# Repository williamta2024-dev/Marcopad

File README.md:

# RP2040 ZERO 4x4 Mechanical Macropad

A custom-built, programmable 16-key mechanical macropad powered by the RP2040 ZERO. This project combines custom PCB design, 3D mechanical modeling, and embedded programming to create a versatile productivity tool.

## Features

* **4x4 Matrix Layout:** 16 fully programmable mechanical switches for shortcuts, macros, or media controls.
* **RP2040 ZERO:** High-performance microcontroller with native USB support.
* **Custom PCB:** Optimized layout for a compact footprint and reliable signal integrity.
* **3D Printed Enclosure:** A custom-designed case tailored specifically for the hardware assembly.
* **Customizable Firmware:** Easily adaptable for various workflows (streaming, coding, gaming).

## Hardware Specifications

| Component | Description |
| :--- | :--- |
| **Microcontroller** | RP2040 ZERO |
| **Switches** | 16x Mechanical Switches (MX-compatible) |
| **PCB** | Custom designed in KiCad |
| **Case** | 3D Printed (ONSHAPE) |
| **Connection** | USB-C |

## Getting Started

### Hardware Assembly
1.  **PCB Fabrication:** Order the PCB using the provided Gerber files in `/hardware/pcb`.
2.  **Soldering:** Solder the RP2040 ZERO and mechanical switches to the PCB.
3.  **Enclosure:** 3D print the top and bottom halves of the enclosure found in `/hardware/enclosure`.
4.  **Final Assembly:** Secure the PCB into the enclosure using M3 screws.

### Firmware Setup
1.  Connect the macropad to your computer via USB-C.
2.  Flash the firmware located in the `/firmware` directory using the Arduino IDE or by copying files if using C++.
3.  Configure your keymaps in the configuration file to match your desired shortcuts. S

### Schematic

### PCB  

### 3D Design

## Bill of Materials (BOM)

Here is the list of components, hardware, and materials required to build this project:

| Item | Component / Part | Description | Qty | Est. Cost | Source / Link |
| :--- | :--- | :--- | :--- | :--- | :--- |
| **1** | MACROPAD PCB-PTH_Y3 | The PCB | 3 | \$7.80 | [Link](https://cart.jlcpcb.com/shopcart/cartEdit/?id=4c4162048d664ba7a7ae664a28d13e49&type=1&changeType=1&achieveDate=48) |
| **2** | Estardyn RP2040-Zero RP2040 for Raspberry Pi Microcontroller PICO Development Board Module Dual-Core 2MB Flash |A raspberry pi for my macropad. | 1 | \$6.71 | [Link](https://www.aliexpress.us/item/3256811972442631.html) |
| **3** |20-100pc Mechanical Keyboard Switches Blue Red Brown Switch Customizable Hot-Swappable 3 Pins Cross Stem for Mechanical Keyboard |Keyswitches for the Macropad | 1 | \$0.99| [Link](https://www.aliexpress.us/item/3256811652574937.html) |
| **4** | 10Pcs/lot M2 M2.5 M3 M3.5 M4 M5 M6 TM Screws Phillips Truss Mushroom Head Screw Black Plated Electronic Carbon Steel Screws| For the PCB to hold in place.| 1 | \$1.57 | [Link](https://www.aliexpress.us/item/32568019372843219.html) |
| **5** | 100PCS/LOT D0-35 1N4148 High-speed Switching Diodes | For the PCB | 1 | \$1.14 | [Link](https://www.aliexpress.us/item/3256802153601411.html) |
| **6** | N3UD 20Pcs PBT Blank Keycap 1U 1X XDA Profile No Print Keycap Set for DIY Mechanical Keyboard Installation MX Switches | Keycaps for the switches | 2 | \$0.99 | [Link](https://www.aliexpress.us/item/3256802153601411.html) |

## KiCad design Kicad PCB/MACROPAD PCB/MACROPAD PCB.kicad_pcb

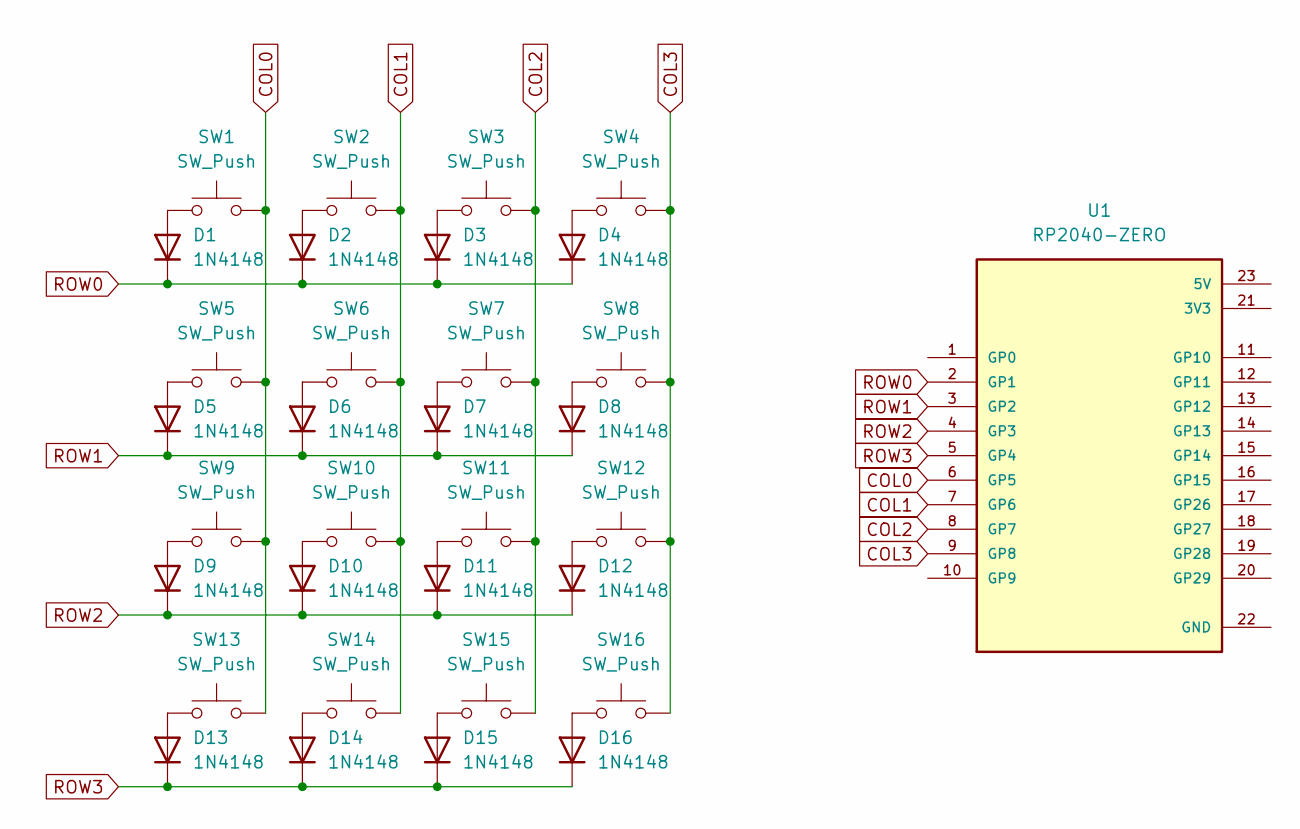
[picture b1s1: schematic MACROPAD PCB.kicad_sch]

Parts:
D1, D2, D3, D4, D5, D6, D7, D8, D9, D10, D11, D12, D13, D14, D15, D16: 1N4148; D_DO-35_SOD27_P7.62mm_Horizontal
SW1, SW2, SW3, SW4, SW5, SW6, SW7, SW8, SW9, SW10, SW11, SW12, SW13, SW14, SW15, SW16: SW_Push; SW_Cherry_MX_1.00u_Plate
U1: RP2040-ZERO; MODULE_RP2040-ZERO; PARTREV NA

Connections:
COL0: SW1.2, SW5.2, SW9.2, SW13.2, U1.6 (GP5)
COL1: SW2.2, SW6.2, SW10.2, SW14.2, U1.7 (GP6)
COL2: SW3.2, SW7.2, SW11.2, SW15.2, U1.8 (GP7)
COL3: SW4.2, SW8.2, SW12.2, SW16.2, U1.9 (GP8)
unnamed: D1.2 (A), SW1.1
unnamed: D2.2 (A), SW2.1
unnamed: D3.2 (A), SW3.1
unnamed: D4.2 (A), SW4.1
unnamed: D5.2 (A), SW5.1
unnamed: D6.2 (A), SW6.1
unnamed: D7.2 (A), SW7.1
unnamed: D8.2 (A), SW8.1
unnamed: D9.2 (A), SW9.1
unnamed: D10.2 (A), SW10.1
unnamed: D11.2 (A), SW11.1
unnamed: D12.2 (A), SW12.1
unnamed: D13.2 (A), SW13.1
unnamed: D14.2 (A), SW14.1
unnamed: D15.2 (A), SW15.1
unnamed: D16.2 (A), SW16.1
ROW0: D1.1 (K), D2.1 (K), D3.1 (K), D4.1 (K), U1.2 (GP1)
ROW1: D5.1 (K), D6.1 (K), D7.1 (K), D8.1 (K), U1.3 (GP2)
ROW2: D9.1 (K), D10.1 (K), D11.1 (K), D12.1 (K), U1.4 (GP3)
ROW3: D13.1 (K), D14.1 (K), D15.1 (K), D16.1 (K), U1.5 (GP4)

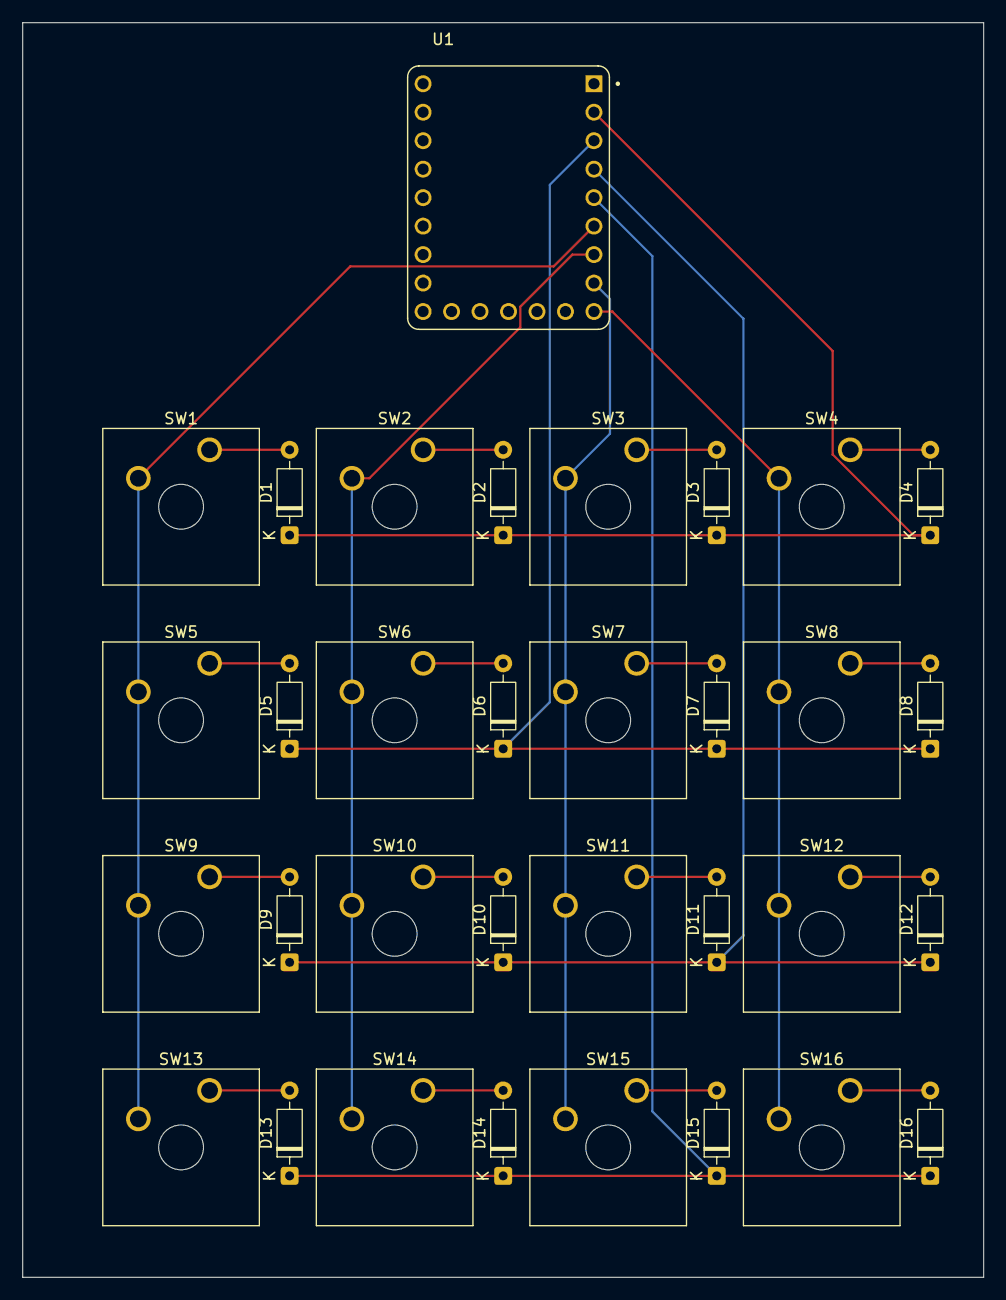
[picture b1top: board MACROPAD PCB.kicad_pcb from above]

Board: 2 copper layers, 85.7 x 111.9 mm, 33 parts (0 on the bottom side), 24 nets.

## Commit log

2026-04-25 Tung
2026-04-25 Schematics
2026-05-06 3D parts
2026-05-07 code
2026-06-03 Fix CSV formatting issues in COMPLETEBOM.csv
2026-06-03 Fix CSV formatting: align columns and add missing distributor values
2026-06-03 delete
2026-06-03 Fix formatting in item list of README
    Fixed formatting issues in the item list, ensuring proper display of costs and links.
2026-06-03 Fix formatting of cost values in README table
